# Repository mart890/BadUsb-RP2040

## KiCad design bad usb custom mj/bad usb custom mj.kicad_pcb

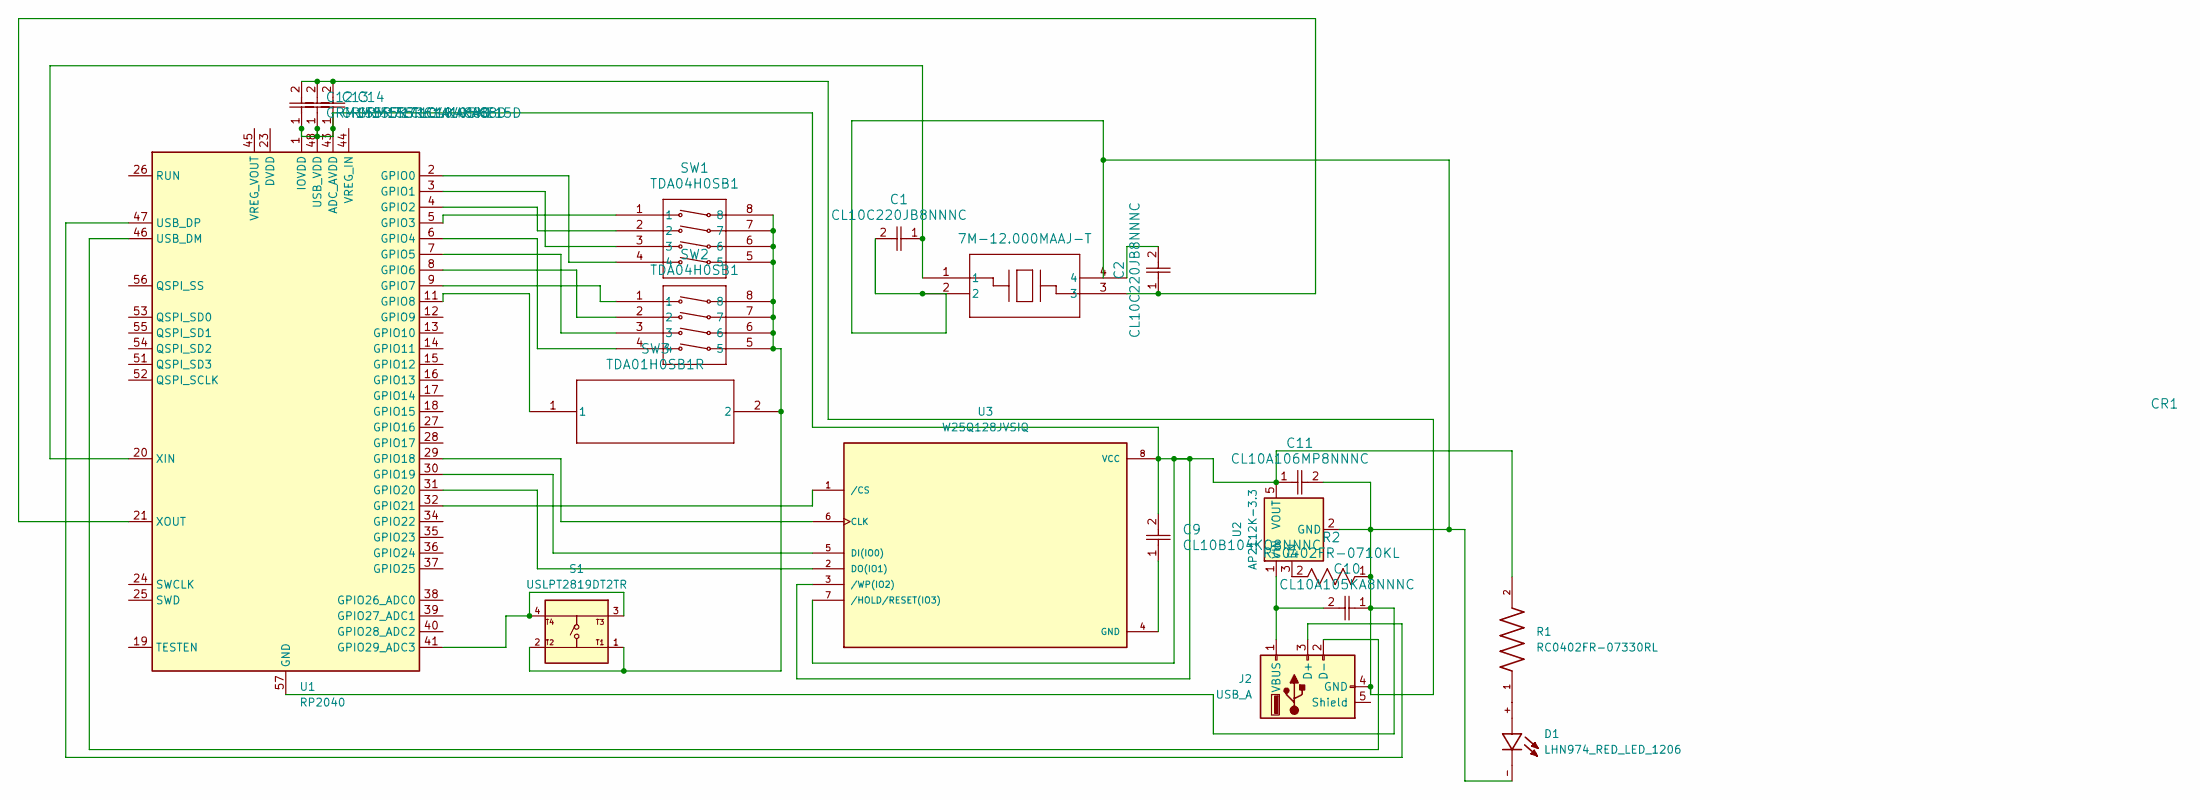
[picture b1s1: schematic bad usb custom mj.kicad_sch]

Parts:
C1, C2: CL10C220JB8NNNC; CAP_CL10_SAM
C9: CL10B104KO8NNNC; CAP_CL10_SAM
C10: CL10A105KA8NNNC; CAP_CL10_SAM
C11: CL10A106MP8NNNC; CAP_CL10_SAM
C12, C13: GRM155R71C104KA88D; CAP_GRM_155_MUR
C14: GRM155R61A105KE15D; CAP_chip2_1X0p5_MUR
CR1: 7M-12.000MAAJ-T; CRYSTAL_TXC_7M
D1: LHN974_RED_LED_1206; LEDC3216X120N; PARTREV 2002-04-11
J2: USB_A; USB_A_CNCTech_1001-011-01101_Horizontal
R1: RC0402FR-07330RL; RESC1005X40N
R2: RC0402FR-0710KL; RC0402N_YAG
S1: USLPT2819DT2TR; SW_USLPT2819DT2TR; PARTREV P
SW1, SW2: TDA04H0SB1; TDA04H0SB1_CNK
SW3: TDA01H0SB1R; SWITCH_0SB1R
U1: RP2040; QFN-56-1EP_7x7mm_P0.4mm_EP3.2x3.2mm
U2: AP2112K-3.3; SOT-23-5
U3: W25Q128JVSIQ; SOIC127P790X216-8N; PARTREV I

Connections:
unnamed: C2.2, CR1.4
unnamed: D1.+, R1.1
unnamed: J2.3 (D+), U1.47 (USB_DP)
unnamed: J2.2 (D-), U1.46 (USB_DM)
unnamed: C1.2, C10.1, C11.2, C12.2, C13.2, C14.2, CR1.2, D1.-, J2.4 (GND), R2.1, U1.57 (GND), U2.2 (GND)
unnamed: C10.2, J2.1 (VBUS), U2.1 (VIN)
unnamed: S1.1, S1.2, SW1.5, SW1.6, SW1.7, SW1.8, SW2.5, SW2.6, SW2.7, SW2.8, SW3.2
unnamed: C9.2, C11.1, C12.1, C13.1, C14.1, R1.2, U1.1 (IOVDD), U1.10 (IOVDD), U1.22 (IOVDD), U1.33 (IOVDD), U1.42 (IOVDD), U1.43 (ADC_AVDD), U1.48 (USB_VDD), U1.49 (IOVDD), U2.5 (VOUT), U3.3 (/WP(IO2)), U3.7 (/HOLD/RESET(IO3)), U3.8 (VCC)
unnamed: U1.23 (DVDD), U1.50 (DVDD)
unnamed: SW1.4, U1.2 (GPIO0)
unnamed: SW1.3, U1.3 (GPIO1)
unnamed: SW1.2, U1.4 (GPIO2)
unnamed: SW1.1, U1.5 (GPIO3)
unnamed: SW2.4, U1.6 (GPIO4)
unnamed: SW2.3, U1.7 (GPIO5)
unnamed: SW2.2, U1.8 (GPIO6)
unnamed: SW2.1, U1.9 (GPIO7)
unnamed: SW3.1, U1.11 (GPIO8)
unnamed: U1.29 (GPIO18), U3.6 (CLK)
unnamed: U1.30 (GPIO19), U3.5 (DI(IO0))
unnamed: U1.31 (GPIO20), U3.2 (DO(IO1))
unnamed: U1.32 (GPIO21), U3.1 (/CS)
unnamed: S1.3, S1.4, U1.41 (GPIO29_ADC3)
unnamed: C1.1, CR1.1, U1.20 (XIN)
unnamed: C2.1, CR1.3, U1.21 (XOUT)
unnamed: R2.2, U2.3 (EN)
unnamed: C9.1, U3.4 (GND)

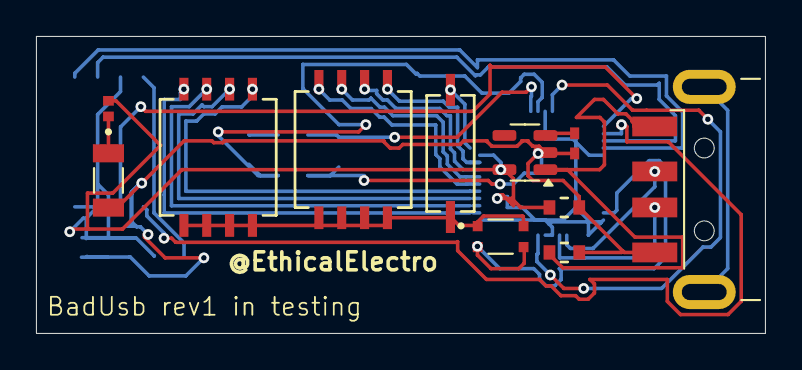
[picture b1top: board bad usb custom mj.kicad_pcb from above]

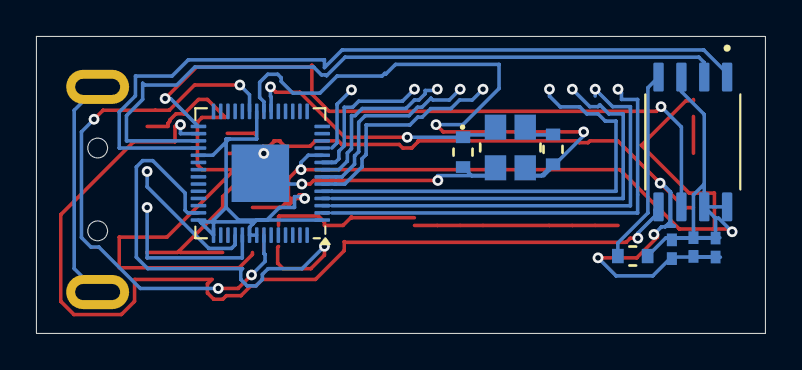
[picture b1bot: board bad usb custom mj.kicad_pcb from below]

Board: 2 copper layers, 40.5 x 16.5 mm, 20 parts (9 on the bottom side), 27 nets.

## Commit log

2025-11-30 project files hope yall like this
    -hope this are all the files I need
